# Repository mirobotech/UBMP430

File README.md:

# UBMP430
 
UBMP430 (USB-Based Beginner Multipurpose Project 4, rev. 3) KiCad schematic and PCB design files.

UBMP430 is a simple, versatile, and inexpensive microcontroller development system for everyone! The UBMP430 circuit board has a variety of simple I/O devices built-in so beginners can learn to code and make an assortment of different projects using just the parts on UBMP430 – no breadboarding, shields, or other modules are required, and external devices can be added using the expansion header. 

UBMP430 was designed for learning or teaching PIC programming in C or assembly language using either Microchip’s MPLAB X IDE or their MPLAB Xpress Cloud-based IDE. The [USB µC bootloader](https://hackaday.io/project/63204-usb-c-usb-pic-bootloader) allows UBMP430 to appear as a mass storage drive for easy programming. Simply drag and drop a compiled .hex file onto the ***PIC16F1459*** drive that shows up in your computer's device manager, and your program will start to run as soon as the file is transferred.

The bootloader makes it possible to program UBMP430 using almost any kind of device, even enabling schools with 1:1 Chromebook programs to teach real C language microcontroller programming with Github integration.

## UBMP430 Hardware Features

- Microchip PIC16F1459 USB-capable microcontroller with 8k words of program FLASH (6k words free when using the USB µC bootloader), 128B of user FLASH, 1kB of RAM, 10-bit ADC, and a built-in temperature sensor
- 5 built-in pushbuttons
- 5 visible light LEDs
- 1 piezo beeper output
- optional 8-pin header for PORTC I/O pin expansion (great for servos, a SONAR module, NeoPixels, an LCD display, etc.)
- optional IR LED output for remote control transmitter applications (or a high-current transistor-driven output)
- optional IR demodulator for remote control decoding
- optional IR phototransistor or visible-light ambient light sensor for light sensing
- USB 2.0 type-C port for power and programming (updated 
- 6-pin ICSP (In-Circuit Serial Programming) header for PICkit-4

## UMBP430 is Open

UBMP430 is open hardware and uses open source software – we want educators to have full access to the circuit, lesson materials, and code. The following permissions and conditions apply to UBMP430:
- the KiCad UBMP430 files stored in GitHub are open hardware licensed under the terms of the MIT license (except the mirobo.tech logo - see below). You are free to use and modify the UBMP430 files to make your own UBMP430 circuit boards.
- UBMP430 programs stored in GitHub are open source software licensed under the terms of the MIT license.
- UMBP430 learning materials on the mirobo.tech website are licensed under the terms of the Creative Commons CC-BY 4.0 license.
- the USB uC bootloader is open source and licensed under the terms of the GPL3.0 license by John Izzard.
- the mirobo.tech logo mark is a trademark of mirobo Technolgy and may not be used without prior permission.

## Can I buy a UBMP430?

UBMP430 boards, kits, and lab packs are available at [mirobo.tech](https://mirobo.tech/ubmp4).  
Bare UBMP430 printed circuit boards are also available from [OSHPARK](https://oshpark.com/shared_projects/tnwOOjI0).

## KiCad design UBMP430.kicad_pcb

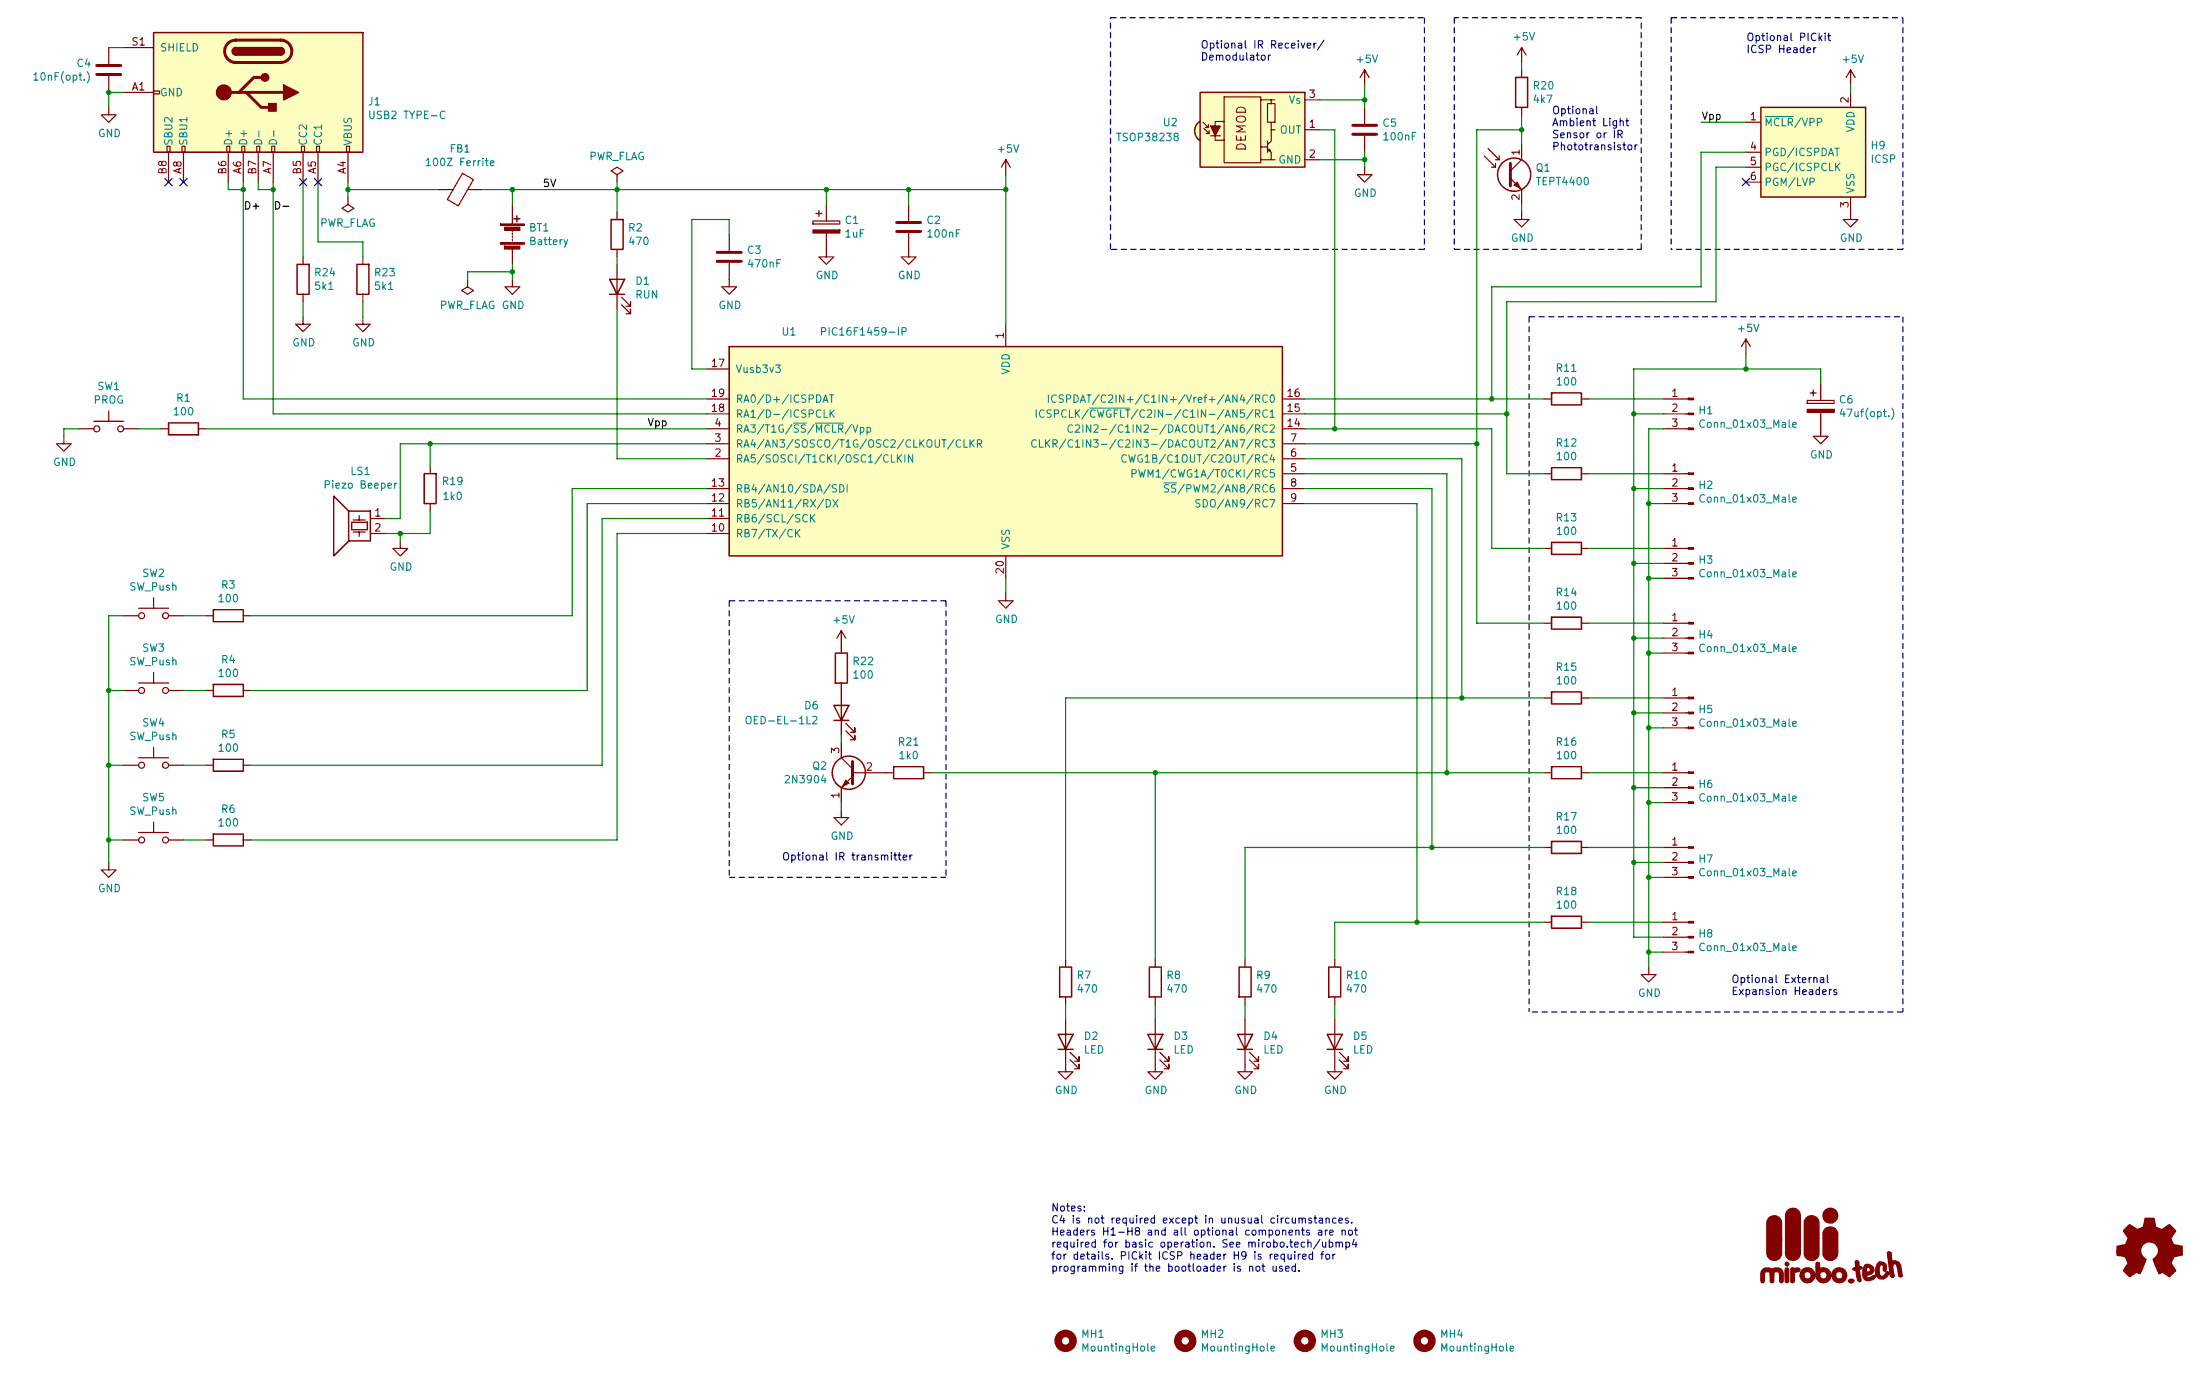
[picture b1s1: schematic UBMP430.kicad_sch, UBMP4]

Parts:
BT1: Battery; PinHeader_1x02_P2.54mm_Vertical
C1: 1uF; CP_Radial_D5.0mm_P2.50mm
C2, C5: 100nF; C_Disc_D3.4mm_W2.1mm_P2.50mm
C3: 470nF; C_Disc_D3.4mm_W2.1mm_P2.50mm
C4: 10nF(opt.); C_Disc_D3.4mm_W2.1mm_P2.50mm
C6: 47uf(opt.); CP_Radial_D6.3mm_P2.50mm
D1: RUN; LED_D3.0mm
D2, D3, D4, D5: LED; LED_D3.0mm
D6: OED-EL-1L2; LED_D5.0mm_Horizontal_O1.27mm_Z3.0mm_Clear
FB1: 100Z Ferrite; R_Axial_DIN0411_L9.9mm_D3.6mm_P12.70mm_Horizontal
G1: mirobotech_logo; mirobo_logo_10
G2: Logo_Open_Hardware_Small; OSHW-Symbol_6.7x6mm_SilkScreen
H1, H2, H3, H4, H5, H6, H7, H8: Conn_01x03_Male; PinHeader_1x03_P2.54mm_Vertical
H9: ICSP; PinHeader_1x06_P2.54mm_Horizontal
J1: USB2 TYPE-C; USB_C_Receptacle_GCT_USB4085
LS1: Piezo Beeper; Buzzer_TDK_PS1240P02BT_D12.2mm_H6.5mm
MH1, MH2, MH3, MH4: MountingHole; MountingHole_3.2mm_M3_Pad
Q1: TEPT4400; LED_D3.0mm_Clear
Q2: 2N3904; TO-92
R1, R3, R4, R5, R6, R11, R12, R13, R14, R15, R16, R17, R18, R22: 100; R_Axial_DIN0207_L6.3mm_D2.5mm_P10.16mm_Horizontal
R2, R7, R8, R9, R10: 470; R_Axial_DIN0207_L6.3mm_D2.5mm_P10.16mm_Horizontal
R19, R21: 1k0; R_Axial_DIN0207_L6.3mm_D2.5mm_P10.16mm_Horizontal
R20: 4k7; R_Axial_DIN0207_L6.3mm_D2.5mm_P10.16mm_Horizontal
R23, R24: 5k1; R_Axial_DIN0207_L6.3mm_D2.5mm_P10.16mm_Horizontal
SW1: PROG; SW_PUSH_6mm
SW2, SW3, SW4, SW5: SW_Push; SW_PUSH_6mm
U1: PIC16F1459-IP; DIP-20_W7.62mm_Socket
U2: TSOP38238; Vishay_MINICAST-3Pin

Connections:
+5V: BT1.1 (+), C1.1, C2.1, C5.1, C6.1, FB1.1, H1.2, H2.2, H3.2, H4.2, H5.2, H6.2, H7.2, H8.2, H9.2 (VDD), R2.2, R20.1, R22.1, U1.1 (VDD), U2.3 (Vs)
/D+: J1.A6 (D+), J1.B6 (D+), U1.19 (RA0/D+/ICSPDAT)
/D-: J1.A7 (D-), J1.B7 (D-), U1.18 (RA1/D-/ICSPCLK)
/Vpp: H9.1 (~MCLR/VPP), R1.2, U1.4 (RA3/T1G/~SS/~MCLR/Vpp)
GND: BT1.2 (-), C1.2, C2.2, C3.2, C4.1, C5.2, C6.2, D2.1 (K), D3.1 (K), D4.1 (K), D5.1 (K), H1.3, H2.3, H3.3, H4.3, H5.3, H6.3, H7.3, H8.3, H9.3 (VSS), J1.A1 (GND), J1.A12 (GND), J1.B1 (GND), J1.B12 (GND), LS1.2, Q1.2 (E), Q2.1 (E), R19.1, R23.1, R24.1, SW1.1, SW2.1, SW3.1, SW4.1, SW5.1, U1.20 (VSS), U2.2 (GND)
unnamed: FB1.2, J1.A4 (VBUS), J1.A9 (VBUS), J1.B4 (VBUS), J1.B9 (VBUS)
unnamed: D1.2 (A), R2.1
unnamed: D1.1 (K), U1.2 (RA5/SOSCI/T1CKI/OSC1/CLKIN)
unnamed: D2.2 (A), R7.2
unnamed: D3.2 (A), R8.2
unnamed: D4.2 (A), R9.2
unnamed: D5.2 (A), R10.2
unnamed: D6.2 (A), R22.2
unnamed: D6.1 (K), Q2.3 (C)
unnamed: H1.1, R11.1
unnamed: H2.1, R12.1
unnamed: H3.1, R13.1
unnamed: H4.1, R14.1
unnamed: H5.1, R15.1
unnamed: H6.1, R16.1
unnamed: H7.1, R17.1
unnamed: H8.1, R18.1
unnamed: H9.5 (PGC/ICSPCLK), R12.2, U1.15 (ICSPCLK/~CWGFLT/C2IN-/C1IN-/AN5/RC1)
unnamed: H9.4 (PGD/ICSPDAT), R11.2, U1.16 (ICSPDAT/C2IN+/C1IN+/Vref+/AN4/RC0)
unnamed: C4.2, J1.S1 (SHIELD)
unnamed: Q1.1 (C), R14.2, R20.2, U1.7 (CLKR/C1IN3-/C2IN3-/DACOUT2/AN7/RC3)
unnamed: Q2.2 (B), R21.2
unnamed: R1.1, SW1.2
unnamed: R3.2, SW2.2
unnamed: R4.2, SW3.2
unnamed: R5.2, SW4.2
unnamed: R6.2, SW5.2
unnamed: R13.2, U1.14 (C2IN2-/C1IN2-/DACOUT1/AN6/RC2), U2.1 (OUT)
unnamed: R7.1, R15.2, U1.6 (CWG1B/C1OUT/C2OUT/RC4)
unnamed: R8.1, R16.2, R21.1, U1.5 (PWM1/CWG1A/T0CKI/RC5)
unnamed: LS1.1, R19.2, U1.3 (RA4/AN3/SOSCO/T1G/OSC2/CLKOUT/CLKR)
unnamed: R3.1, U1.13 (RB4/AN10/SDA/SDI)
unnamed: R4.1, U1.12 (RB5/AN11/RX/DX)
unnamed: R5.1, U1.11 (RB6/SCL/SCK)
unnamed: R6.1, U1.10 (RB7/TX/CK)
unnamed: R10.1, R18.2, U1.9 (SDO/AN9/RC7)
unnamed: C3.1, U1.17 (Vusb3v3)
unnamed: R9.1, R17.2, U1.8 (~SS/PWM2/AN8/RC6)

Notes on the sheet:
Notes: C4 is not required except in unusual circumstances. Headers H1-H8 and all optional components are not required for basic operation. See mirobo.tech/ubmp4 for details. PICkit ICSP header H9 is required for programming if the bootloader is not used.
Optional IR transmitter
Optional External Expansion Headers
Optional Ambient Light Sensor or IR Phototransistor
Optional IR Receiver/ Demodulator
Optional PICkit ICSP Header

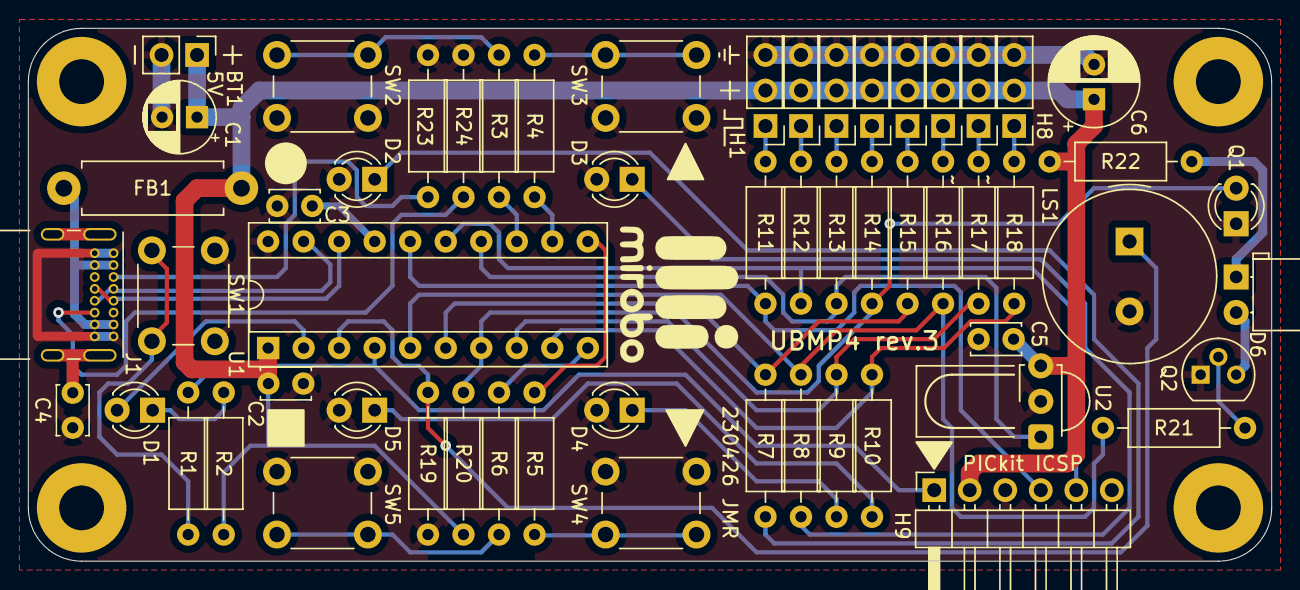
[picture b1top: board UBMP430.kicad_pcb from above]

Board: 2 copper layers, 88.9 x 38.1 mm, 64 parts (1 on the bottom side), 43 nets.

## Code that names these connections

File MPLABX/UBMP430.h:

/* =============================================================================
 * File: UBMP430.h
 * Date: January 20, 2026
 * 
 * UBMP4.3 hardware definitions and function prototypes (PIC16F1459 in USB mode)
 * ===========================================================================*/

#ifndef UBMP430_H
#define UBMP430_H

#define _XTAL_FREQ  48000000UL      // Set clock frequency for timing functions

/* =====================================
 * UBMP4 hardware definitions
 * ===================================== */

// PORTA
#define MCLR        PORTAbits.RA3   // SW1/PROG/Reset (MCLR) pushbutton input
#define SW1         PORTAbits.RA3   // SW1/PROG/Reset (MCLR) pushbutton input
#define BEEPER      LATAbits.LATA4  // Piezo beeper (LS1) output
#define	LS1         LATAbits.LATA4  // Piezo beeper (LS1) output
#define LED1        LATAbits.LATA5  // LED D1/Run LED output (active-low)

// PORTB I/O
#define SW2         PORTBbits.RB4   // Pushbutton SW2 input
#define SW3         PORTBbits.RB5   // Pushbutton SW3 input
#define SW4         PORTBbits.RB6   // Pushbutton SW4 input
#define SW5         PORTBbits.RB7   // Pushbutton SW5 input

// PORTC
#define H1IN        PORTCbits.RC0   // External I/O header H1 input
#define H1OUT       LATCbits.LATC0  // External I/O header H1 output

#define H2IN        PORTCbits.RC1   // External I/O header H2 input
#define H2OUT       LATCbits.LATC1  // External I/O header H2 output

#define H3IN        PORTCbits.RC2   // External I/O header H3 input
#define H3OUT       LATCbits.LATC2  // External I/O header H3 output 
#define U2          PORTCbits.RC2   // IR demodulator (U2) input

#define H4IN        PORTCbits.RC3   // External I/O header H4 input
#define H4OUT       LATCbits.LATC3  // External I/O header H4 output
#define Q1          PORTCbits.RC3   // Phototransistor/ambient light sensor (Q1) input

#define H5IN        PORTCbits.RC4   // External I/O header H5 input
#define H5OUT       LATCbits.LATC4  // External I/O header H5 output
#define LED2        LATCbits.LATC4  // LED D2 output

#define H6IN        PORTCbits.RC5   // External I/O header H6 input
#define H6OUT       LATCbits.LATC5  // External I/O header H6 output
#define LED3        LATCbits.LATC5  // LED D3 output
#define LED6        LATCbits.LATC5  // LED D6/IR LED output

#define H7IN        PORTCbits.RC6   // External I/O header H7 input
#define H7OUT       LATCbits.LATC6  // External I/O header H7 output
#define LED4        LATCbits.LATC6  // LED D4 output

#define H8IN        PORTCbits.RC7   // External I/O header H8 input
#define H8OUT       LATCbits.LATC7  // External I/O header H8 output
#define LED5        LATCbits.LATC7  // LED D5 output

/* =====================================
 * ADC channel definitions
 * ===================================== */

#define A3          0b00001100      // A-D converter channel 3 input (LS1)
#define AH1         0b00010000      // External H1 header analogue input (Ch4))
#define A4          0b00010000      // A-D converter channel 4 input
#define AH2         0b00010100      // External H2 header analogue input (Ch5)
#define A5          0b00010100      // A-D converter channel 5 input
#define AH3         0b00011000      // External H3 header analogue input (Ch6)
#define A6          0b00011000      // A-D converter channel 6 input
#define AH4         0b00011100      // External H4 header analogue input (Ch7)
#define A7          0b00011100      // A-D converter channel 7 input
#define AQ1         0b00011100      // Q1 phototransistor A-D input (Ch7)
#define AH7         0b00100000      // External H7 header analogue input (Ch8)
#define A8          0b00100000      // A-D converter channel 8 input
#define AH8         0b00100100      // External H8 header analogue input (Ch9)
#define A9          0b00100100      // A-D converter channel 9 input
#define A10         0b00101000      // A-D converter channel 10 input (SW2 - not used)
#define A11         0b00101100      // A-D converter channel 11 input (SW3 - not used)
#define ATIM        0b01110100      // On-die temperature indicator module input
#define ADAC        0b01111000      // Internal DAC (digital-to-analog converter)
#define AFVR        0b01111100      // Internal fixed voltage reference buffer

/* =====================================
 * Core UBMP4/PIC16F1459 initialization
 * ===================================== */

void UBMP4_Init(void);


/* =====================================
 * Timing functions
 * ===================================== */

void delay_ms(uint16_t ms);
/* Delays for specified number of milliseconds.
 * parameter(s): ms (unsigned int) - number of milliseconds to delay (blocking)
 * returns: nothing
 */

void delay_us(uint16_t us);
/* Delays for specified number of microseconds.
 * parameter(s): us (unsigned int) - number of microseconds to delay (blocking)
 * returns: nothing
 */

uint32_t millis(void);
/* Interrupt-drive milliseconds counter.
 * parameter(s): none
 * returns: milliseconds (unsigned long) since microcontroller start-up
 */


/* =====================================
 * ADC functions
 * ===================================== */

void ADC_Init(void);
/* Configures ADC converter and GPIO to read from on-board phototransistor Q1 (AN7).
 * parameter(s): none
 * returns: nothing
 */

void ADC_Set_Channel(uint8_t channel);
/* Sets ADC input mux to the selected channel.
 * parameter(s): channel constant (unsigned char) encoded with channel select (CHS) bits
 * returns: nothing
 */
uint16_t ADC_Read(void);
/* Reads 10-bit result from currently selected ADC input channel.
 * parameter(s): nothing
 * returns: digital value equivalent to analog input level (10-bits, unsigned int)
 */

uint8_t ADC_Read_8bits(void);
/* Reads 8-bit result from currently selected ADC input channel.
 * parameter(s): nothing
 * returns: digital value equivalent to analog input level (8-bits, unsigned char)
 */

uint16_t ADC_Read_Channel(uint8_t channel);
/* Sets ADC input mux to selected ADC imput channel and reads the 10-bit result.
 * parameter(s): channel constant (unsigned char) encoded with channel select (CHS) bits
 * returns: digital value equivalent to analog input level (10-bits, unsigned int)
 */


/* =====================================
 * PWM functions
 * ===================================== */

void PWM1_Start(uint16_t freq);
/* Starts 50% duty cycle PWM1 output using Timer 2 hardware module (designed for
 * producing 38kHz output for IR transmission).
 * parameter(s): freq (unsigned int) - PWM frequency in Hz (minimum 11765)
 * returns: nothing
 */

void PWM1_On(void);
/* Restarts PWM1 output.
 * parameter(s): none
 * returns: nothing
 */

void PWM1_Off(void);
/* Stops PWM1 output.
 * parameter(s): none
 * returns: nothing
 */

void PWM1_Stop(void);
/* Stops PWM1 output and disables Timer 2.
 * parameter(s): none
 * returns: nothing
 */


/* =====================================
 * Sound function
 * ===================================== */

void play_Freq(uint16_t freq, uint32_t ms);
/* Plays a tone on the piezo buzzer for the requested amount of time.
 * parameter(s): freq (unsigned int) - tone frequency in Hertz
 *               ms (unsigned int) - tone duration in milliseconds (blocking)
 * returns: nothing
 */


/* =====================================
 * Map function
 * ===================================== */

int16_t map(int16_t value, int16_t min, int16_t max, int16_t newMin, int16_t newMax);
/* Maps a numeric value from an intial input range into a new output range.
 * parameter(s): value (int) - initial value
 *               min (int) - input range minimum value
 *               max (int) - input range maximum value
 *               newMin (int) - output range minimum value
 *               newMax (int) - output range maximum value
 * returns: output result (int)
 */

#endif

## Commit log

2023-04-26 Update README.md with parts list
2026-01-20 Added MPLABX example program

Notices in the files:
UBMP430.kicad_pcb:
Drawings: CC-BY 4.0
UBMP430.kicad_sch:
Schematic: CC-BY 4.0
